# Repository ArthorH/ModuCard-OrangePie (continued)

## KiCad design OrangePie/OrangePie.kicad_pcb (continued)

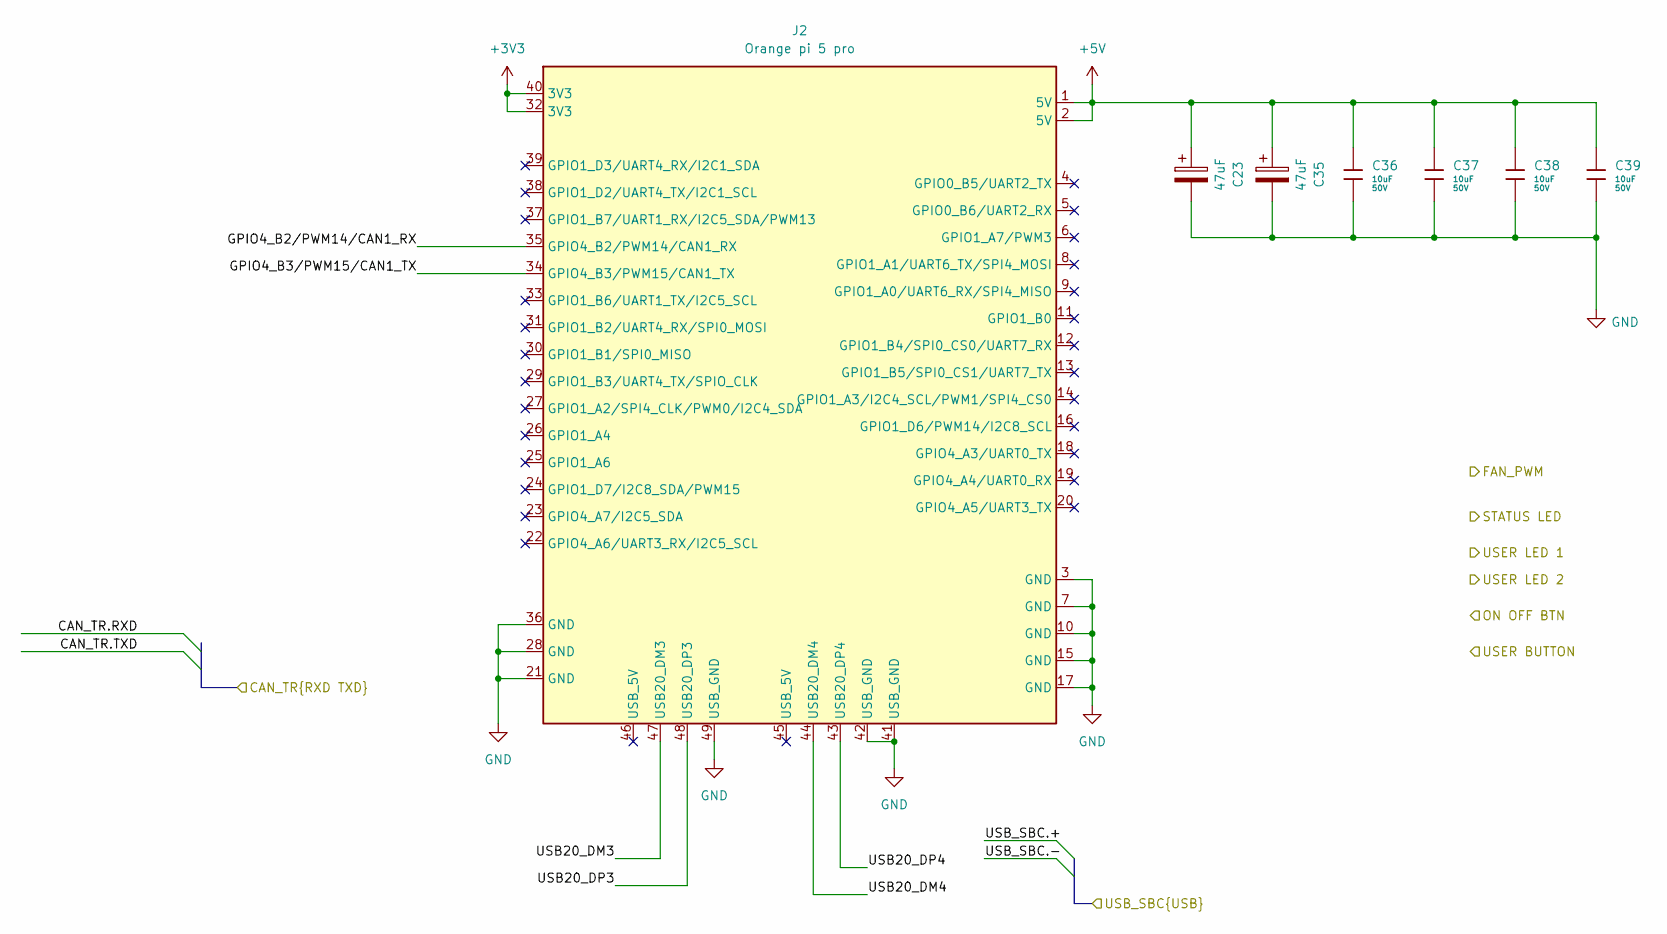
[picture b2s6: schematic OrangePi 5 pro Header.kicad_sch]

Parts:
C23, C35: 47uF; CP_Elec_6.3x5.4; MPN VT1V470M0605; LCSC C90276
C36, C37, C38, C39: 10uF; C_1206; Voltage Rated 50V; Tolerance ±10%; Part CL31A106KBHNNNE; LCSC C13585
J2: Orange pi 5 pro; Orange Pi 5 pro

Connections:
+3V3: J2.32 (3V3), J2.40 (3V3); also elsewhere on the board
+5V: C23.1, C35.1, C36.1, C37.1, C38.1, C39.1, J2.1 (5V), J2.2 (5V); also elsewhere on the board
/OrangePi 5 pro Header/GPIO4_B2/PWM14/CAN1_RX: J2.35 (GPIO4_B2/PWM14/CAN1_RX)
/OrangePi 5 pro Header/GPIO4_B3/PWM15/CAN1_TX: J2.34 (GPIO4_B3/PWM15/CAN1_TX)
/OrangePi 5 pro Header/USB20_DM3: J2.47 (USB20_DM3)
/OrangePi 5 pro Header/USB20_DM4: J2.44 (USB20_DM4)
/OrangePi 5 pro Header/USB20_DP3: J2.48 (USB20_DP3)
/OrangePi 5 pro Header/USB20_DP4: J2.43 (USB20_DP4)
GND: C23.2, C35.2, C36.2, C37.2, C38.2, C39.2, J2.3 (GND), J2.7 (GND), J2.10 (GND), J2.15 (GND), J2.17 (GND), J2.21 (GND), J2.28 (GND), J2.36 (GND), J2.41 (USB_GND), J2.42 (USB_GND), J2.49 (USB_GND); also elsewhere on the board

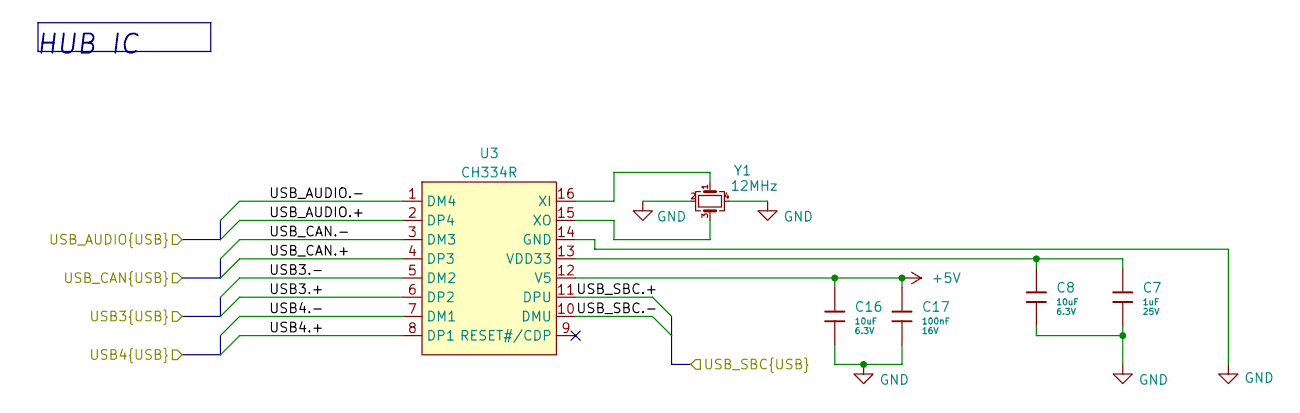
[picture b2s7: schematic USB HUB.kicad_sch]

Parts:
C7: 1uF; C_0402; Voltage Rated 25V; Tolerance ±10%; Part CL05A105KA5NQNC; LCSC C52923
C8, C16: 10uF; C_0402; Voltage Rated 6.3V; Tolerance ±20%; Part CL05A106MQ5NUNC; LCSC C15525
C17: 100nF; C_0402; Voltage Rated 16V; Tolerance ±10%; Part CL05B104KO5NNNC; LCSC C1525
U3: CH334R; QSOP-16_3.9x4.9mm_P0.635mm
Y1: 12MHz; Crystal_SMD_3225-4Pin_3.2x2.5mm

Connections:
+5V: C16.1, C17.1, U3.12 (V5); also elsewhere on the board
/Audio Codec/USB_AUDIO.+: U3.2 (DP4); also elsewhere on the board
/Audio Codec/USB_AUDIO.-: U3.1 (DM4); also elsewhere on the board
/OrangePi 5 pro Header/USB_SBC.+: U3.11 (DPU)
/OrangePi 5 pro Header/USB_SBC.-: U3.10 (DMU)
/USB HUB/USB3.+: U3.6 (DP2)
/USB HUB/USB3.-: U3.5 (DM2)
/USB HUB/USB4.+: U3.8 (DP1)
/USB HUB/USB4.-: U3.7 (DM1)
/USB HUB/USB_CAN.+: U3.4 (DP3); also elsewhere on the board
/USB HUB/USB_CAN.-: U3.3 (DM3); also elsewhere on the board
GND: C7.2, C8.2, C16.2, C17.2, U3.14 (GND), Y1.2, Y1.4; also elsewhere on the board
unnamed: C7.1, C8.1, U3.13 (VDD33)
unnamed: U3.16 (XI), Y1.1
unnamed: U3.15 (XO), Y1.3

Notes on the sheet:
HUB IC

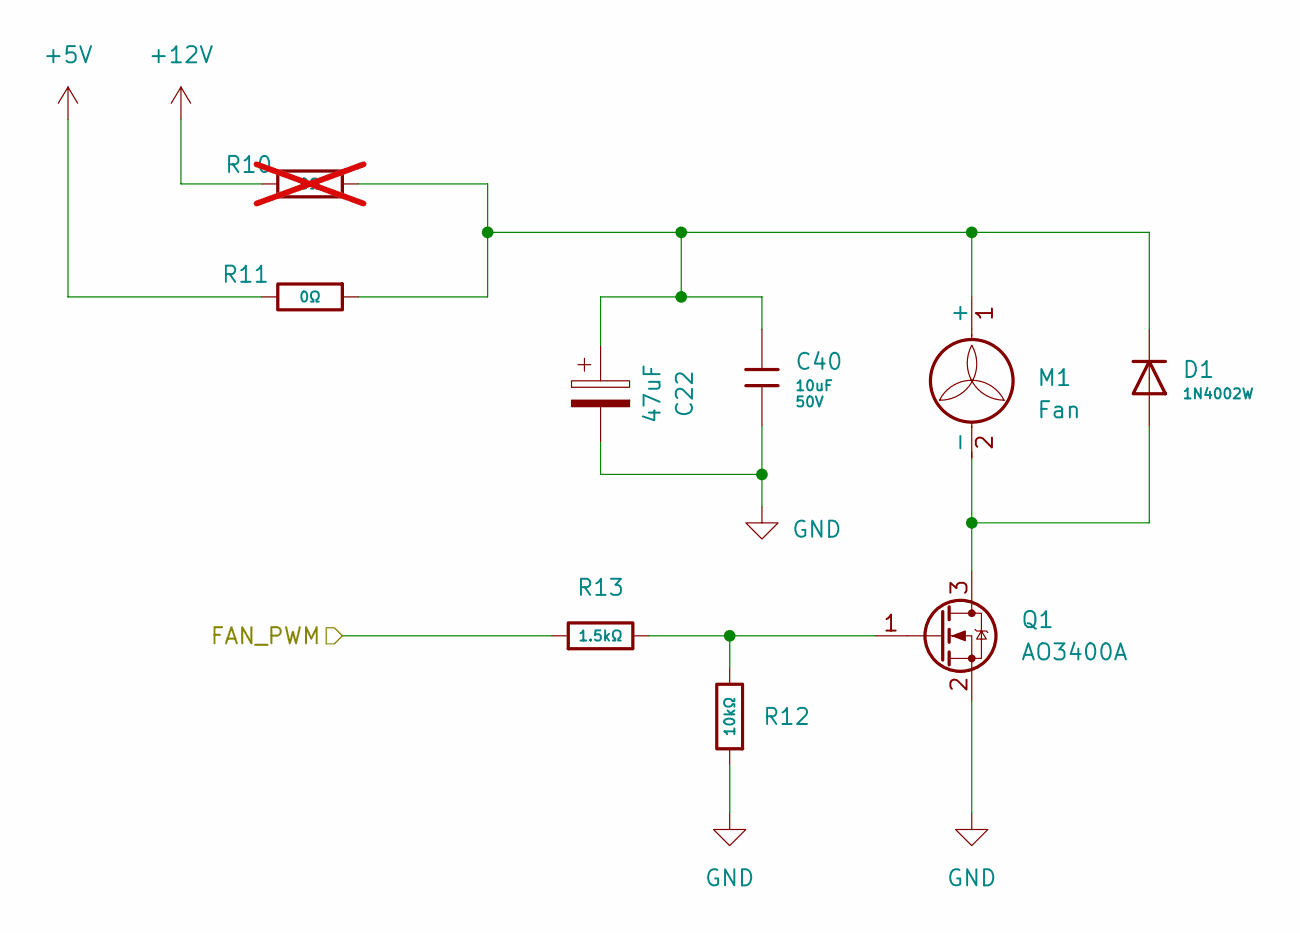
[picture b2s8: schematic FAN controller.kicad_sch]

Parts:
C22: 47uF; CP_Elec_6.3x5.4; MPN VT1V470M0605; LCSC C90276
C40: 10uF; C_1206; Voltage Rated 50V; Tolerance ±10%; Part CL31A106KBHNNNE; LCSC C13585
D1: 1N4002W; D_SOD-123FL; Forward Voltage (Vf@If) 1V@1.0A; Reverse Voltage (Vr) 100V; Part 1N4002W; LCSC C18199086
M1: Fan; JST_XH_B2B-XH-AM_1x02_P2.50mm_Vertical
Q1: AO3400A; SOT-23
R10: 0Ω; R_0402; Overload Voltage (Max) 50V; Tolerance ±1%; Part 0402WGF0000TCE; LCSC C17168; not fitted
R11: 0Ω; R_0402; Overload Voltage (Max) 50V; Tolerance ±1%; Part 0402WGF0000TCE; LCSC C17168
R12: 10kΩ; R_0402; Overload Voltage (Max) 50V; Tolerance ±1%; Part 0402WGF1002TCE; LCSC C25744
R13: 1.5kΩ; R_0402; Overload Voltage (Max) 50V; Tolerance ±1%; Part 0402WGF1501TCE; LCSC C25867

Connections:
+5V: R11.2; also elsewhere on the board
/FAN controller/FAN_PWM: R13.1
GND: C22.2, C40.2, Q1.2 (S), R12.1; also elsewhere on the board
unnamed: C22.1, C40.1, D1.1, M1.1 (+), R10.1, R11.1
unnamed: D1.2, M1.2 (-), Q1.3 (D)
unnamed: Q1.1 (G), R12.2, R13.2

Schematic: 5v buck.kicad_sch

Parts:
C24, C26: 100nF 50V Y5V; C_0402_1005Metric
C25: 10uF 50v; C_0805_2012Metric
C27, C28, C29, C30: 10uF; C_1206; Voltage Rated 50V; Tolerance ±10%; Part CL31A106KBHNNNE; LCSC C13585
C31, C32: 1uF 25V; C_0402_1005Metric
C41: 47uF; CP_Elec_6.3x5.4; MPN VT1V470M0605; LCSC C90276
L1: 6.8uH 12.5x12.5mm; L_AVX_LMLP07A7; MPN YSPI0740-6R8M
R14: 39k 1%; R_0402_1005Metric
R15: 31.6k 1%; R_0402_1005Metric
R16, R17: 10k 1%; R_0402_1005Metric
U6: Diodes_SO-8EP

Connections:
/5v buck/5V_OUT: C27.1, C28.1, C29.1, C30.1, L1.2, R15.1; also elsewhere on the board
GND: C25.2, C26.2, C27.2, C28.2, C29.2, C30.2, C31.1, C32.1, C41.2, R16.2, R17.2, U6.9 (EPAD); also elsewhere on the board
unnamed: C24.1, U6.1 (BST)
unnamed: R14.2, R16.1, U6.3 (EN)
unnamed: R15.2, R17.1, U6.5 (FB)
unnamed: C24.2, L1.1, U6.2 (Lx)
unnamed: C32.2, U6.4 (SS)
unnamed: C31.2, U6.6 (VCC)

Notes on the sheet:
1.2v tresh
6v UVLO

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
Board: 2 copper layers, 99 parts (1 on the bottom side), 51 nets, no tracks yet.

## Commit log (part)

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2025-02-08 Add base schematic and PCM audio interface
2025-02-08 Add usb hub and can tranceiver
2025-02-09 Update rest of schematic
2025-02-10 Add CH340 debug
2025-02-15 Do Cleanup
2025-02-15 Fix audio codec schematic
2025-02-15 Figure out SSPND pin
2025-02-15 Pass ERC
2025-02-15 Prepare board for layout
2025-02-16 Do buck Layout
2025-02-18 Create v1 floorplan
2025-02-20 Do signal layer layout
2025-02-20 Finish layout
2025-02-20 Add silk
2025-02-20 Change speaker holes position
2025-02-21 Prepare for boardhouse
2025-02-21 Add 22R resistors to USB
2025-02-21 Check BOM and add tooling holes
2025-02-22 Make ready for fabrication
2025-02-23 Edit block diagram
2025-02-23 Fix readme formatting bug
2025-03-06 Fix trypo
2025-04-20 Fix schematic
2025-04-20 [3] Start layout
2025-04-20 [3] Finish pcb
2025-04-20 Bump revision
2025-04-20 [3] Bump revision
2025-05-24 production ready
2025-09-24 Fix can power delivery , fixed placment of the mosfets, CAN power pull down to avoid DFU boot, added new porgraming connector
